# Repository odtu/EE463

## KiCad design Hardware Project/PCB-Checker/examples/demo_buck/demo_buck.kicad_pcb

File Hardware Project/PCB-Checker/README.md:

# EE463 PCB Checker

Checks your **EE463 DC–DC converter** board before you send it to the fab, and shows the result in your browser. It works offline and needs only KiCad (8, 9 or 10).

## How to use

**Check your KiCad board or your submission zip (Windows):**
drag your `.kicad_pcb` file, project folder or submission `.zip` onto **`check_pcb.bat`**.

**Check inside KiCad:** install the button once. See [kicad_plugin/README.md](kicad_plugin/README.md).

**Command line (any system):**

```bash
python check_pcb.py MyBoard.kicad_pcb --open
```

Add `--overload` to check for the 7.5 A bonus.

Before you submit, run it on **the zip you will send**. It also checks that the Gerbers, drill files, schematic, PCB file and BOM are all there.

## What it checks

- **Manufacturing (PCBWay standard price):** track width, spacing, holes, copper near the edge, board outline, layers.
- **Power stage:** track width for 5 A, spacing for 48 V, capacitor voltage ratings, the input capacitor at the switches, the gate driver close to the MOSFETs, feedback routing, nothing routed under the inductor.
- **Testing:** test points on ground, gate signals and supplies; parts big enough to solder by hand.
- **KiCad DRC.**

If you use another EDA tool, only the manufacturing checks run, from your Gerber files.

## Reading the report

- **Red (must fix):** the board can't be made or will fail.
- **Orange (should fix):** fix it, or be ready to explain why.
- **Blue (check):** look at it yourself.

At the top, check that **"What the checker found on your board"** is right (input, switch node, output). Click a problem to see where it is on the board. At the end, go through **"Check these yourself"**.

## Example

`examples/demo_buck` is a small buck converter with mistakes in it on purpose. Run the checker on it to see a report.

## Contact

Questions or problems: [wa.me/ekremturanfirat](https://wa.me/ekremturanfirat)

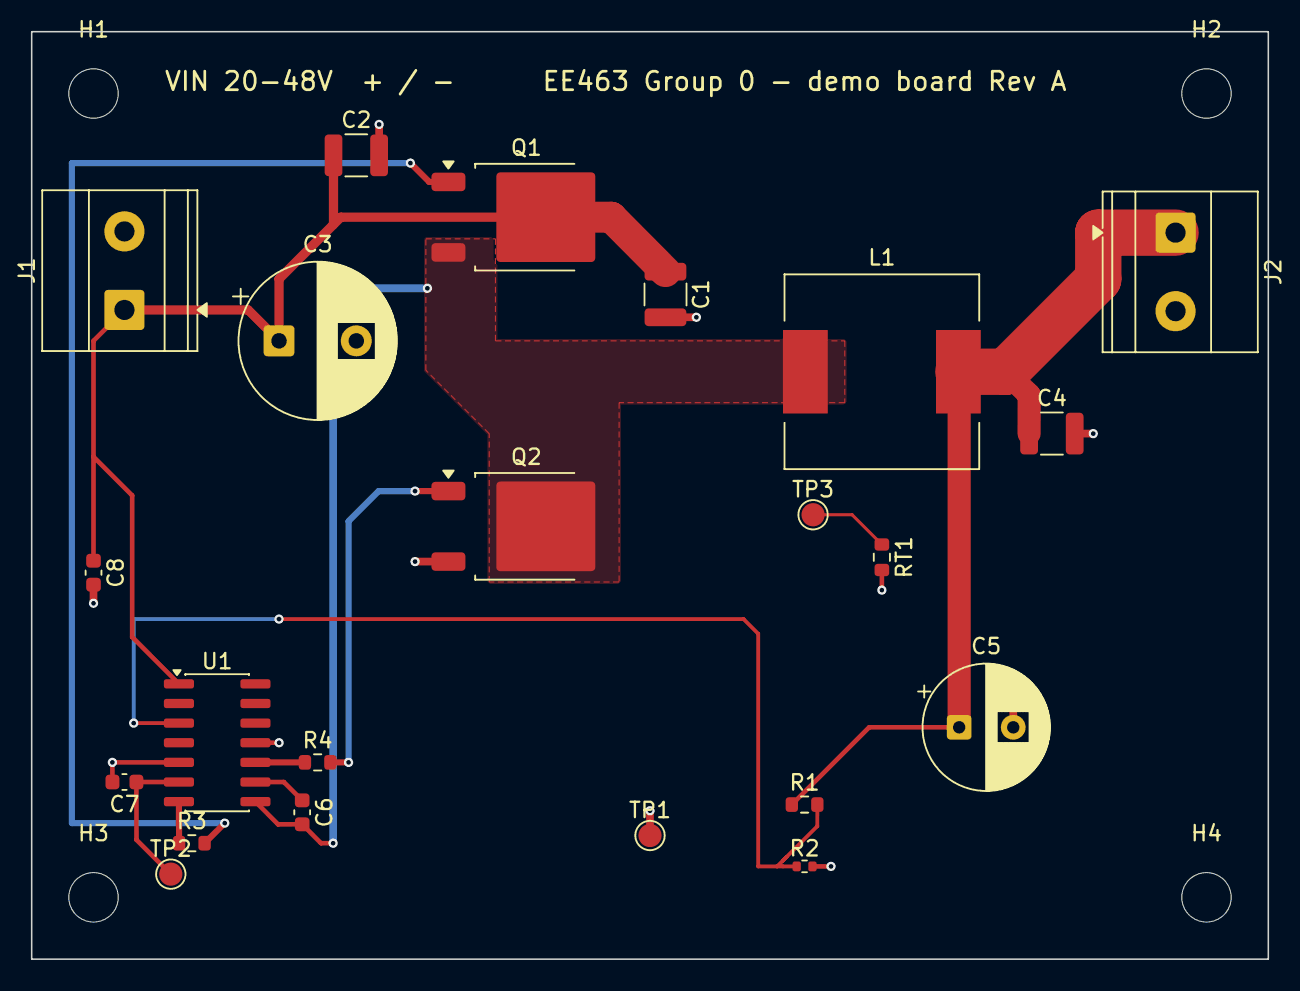
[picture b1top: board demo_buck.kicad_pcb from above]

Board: 2 copper layers, 80.0 x 60.0 mm, 26 parts (0 on the bottom side), 12 nets.

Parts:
C1: 4.7uF 100V; C_1210_3225Metric
C2: 4.7uF 50V; C_1210_3225Metric
C3: 100uF 63V; CP_Radial_D10.0mm_P5.00mm
C4: 47uF 25V; C_1210_3225Metric
C5: 470uF 10V; CP_Radial_D8.0mm_P3.50mm
C6: 100nF 25V; C_0603_1608Metric
C7: 1uF 25V; C_0603_1608Metric
C8: 100nF 100V; C_0603_1608Metric
H1, H2, H3, H4: M3; MountingHole_3.2mm_M3
J1: VIN; TerminalBlock_Phoenix_MKDS-1,5-2-5.08_1x02_P5.08mm_Horizont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
J2: VOUT; TerminalBlock_Phoenix_MKDS-1,5-2-5.08_1x02_P5.08mm_Horizont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
L1: 15uH 10A; L_12x12mm_H8mm
Q1, Q2: BSC100N10; TO-252-2
R1: 100k; R_0603_1608Metric
R2: 7.15k; R_0402_1005Metric
R3, R4: 2.2; R_0603_1608Metric
RT1: 10k NTC; R_0603_1608Metric
TP1: GND; TestPoint_Pad_D1.5mm
TP2: VCC; TestPoint_Pad_D1.5mm
TP3: NTC; TestPoint_Pad_D1.5mm
U1: LM5145; SOIC-14_3.9x8.7mm_P1.27mm

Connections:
FB: R1.2, R2.1, U1.3 (FB)
GH: Q1.1 (G), R3.2
GL: Q2.1 (G), R4.2
GND: C1.2, C2.2, C3.2, C4.2, C5.2, C7.2, C8.2, J1.2, J2.2, Q2.3 (S), R2.2, RT1.2, TP1.1, U1.5 (AGND), U1.11 (PGND)
HB: C6.1, U1.9 (HB)
HO_R: R3.1, U1.7 (HO)
LO_R: R4.1, U1.10 (LO)
NTC: RT1.1, TP3.1
SW: C6.2, L1.1, Q1.3 (S), Q2.2 (D), U1.8 (SW)
VCC: C7.1, TP2.1, U1.6 (VCC)
VIN: C1.1, C2.1, C3.1, C8.1, J1.1, Q1.2 (D), U1.1 (VIN)
VOUT: C4.1, C5.1, J2.1, L1.2, R1.1
